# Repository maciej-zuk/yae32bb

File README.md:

# yae32bb
https://hackaday.io/project/25200-yet-another-esp-32-wroom-breakout-board

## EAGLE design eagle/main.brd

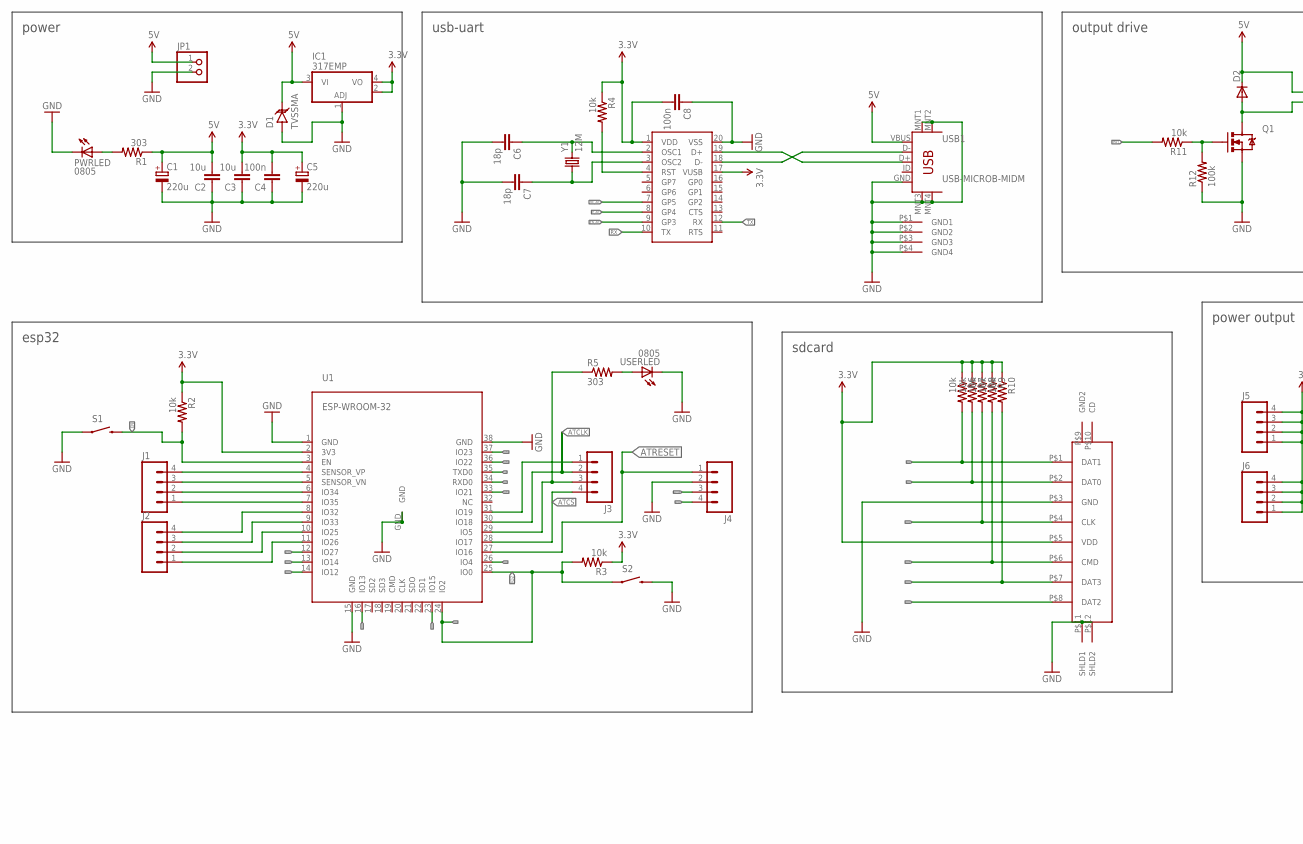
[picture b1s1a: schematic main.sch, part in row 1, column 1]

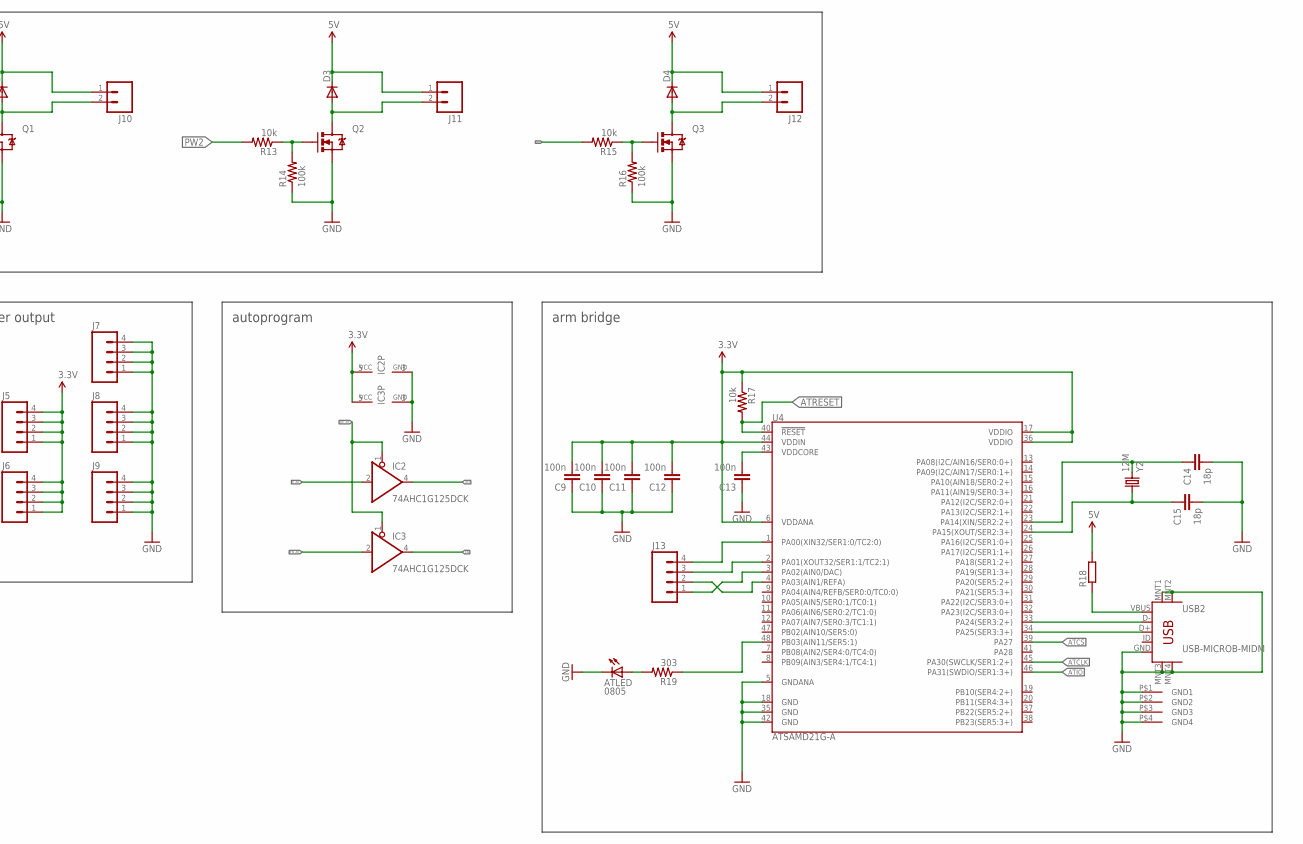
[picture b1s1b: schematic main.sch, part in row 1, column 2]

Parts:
ATLED: 0805; SML0805
C1, C5: 220u; E2-4
C2, C3: 10u; 0805
C4, C8: 100n; 0603-CAP
C6, C7, C14, C15: 18p; 0603-CAP
C9, C10, C11, C12, C13: 100n; C0603K
D1: TVSSMA; SMA-DIODE
D2, D3, D4: DIODE-SOD323-W; SOD323-W
IC1: 317EMP; SOT223
IC2, IC3: 74AHC1G125DCK; SC70-5
J1, J2, J5, J6, J7, J8, J9: M04LONGPADS; 1X04_LONGPADS
J3, J4, J13: M041.27MM; 1X04-1.27MM
J10, J11, J12: M02LOCK_LONGPADS; 1X02_LOCK_LONGPADS
JP1: PINHD-1X2; 1X02
PWRLED: 0805; SML0805
Q1, Q2, Q3: MOSFET-NCHANNELBSS138; SOT23-3
R1, R5, R19: 303; 0805
R2, R3, R4, R6, R7, R8, R9, R10, R11, R13, R15, R17: 10k; 0805
R12, R14, R16: 100k; 0805
R18: R-EU_R2010W; R2010W
S1, S2: SWITCH-MOMENTARY-2SMD; TACTILE-SWITCH-SMD
U1: ESP-WROOM-32
U2: MCP2200; SO20W
U3: MICROSD
U4: ATSAMD21G-A; TQFP-48
USB1, USB2: USB-MICROB-MIDM; USB-B-MICRO-MIDM
USERLED: 0805; SML0805
Y1, Y2: 12M; CRYSTAL-TXC-7A

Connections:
3.3V: C3.2, C4.2, C5.+, C8.2, C9.2, C10.2, C11.2, C12.2, IC1.2 (VO2), IC1.4 (VO), IC2.5 (VCC), IC3.5 (VCC), J5.1, J5.2, J5.3, J5.4, J6.1, J6.2, J6.3, J6.4, R2.1, R3.1, R4.1, R6.1, R7.1, R8.1, R9.1, R10.1, R17.1, U1.2 (3V3), U2.1 (VDD), U2.17 (VUSB), U3.P$5 (VDD), U4.6 (VDDANA), U4.17 (VDDIO), U4.36 (VDDIO), U4.44 (VDDIN)
5V: C1.+, C2.2, D1.C, D2.C, D3.C, D4.C, IC1.3 (VI), J10.1, J11.1, J12.1, JP1.1, R1.1, R18.2, USB1.VBUS
ATCLK: J3.2, J4.3, U1.30 (IO18), U4.45 (PA30(SWCLK/SER1:2+))
ATCS: J3.4, U1.28 (IO17), U4.39 (PA27)
ATIO: J4.4, U1.12 (IO27), U4.46 (PA31(SWDIO/SER1:3+))
ATRESET: J4.1, R17.2, U1.27 (IO16), U4.40 (!RESET!)
D+: U2.19 (D+), USB1.D+
D-: U2.18 (D-), USB1.D-
EN: IC3.4 (O), R2.2, S1.3 (2), U1.3 (EN)
EN_AP: IC3.2 (I), U2.9 (GP3)
GND: ATLED.C, C1.-, C2.1, C3.1, C4.1, C5.-, C6.2, C7.2, C8.1, C9.1, C10.1, C11.1, C12.1, C13.1, C14.2, C15.2, D1.A, IC1.1 (ADJ), IC2.3 (GND), IC3.3 (GND), J4.2, J7.1, J7.2, J7.3, J7.4, J8.1, J8.2, J8.3, J8.4, J9.1, J9.2, J9.3, J9.4, JP1.2, PWRLED.C, Q1.2 (S), Q2.2 (S), Q3.2 (S), R12.1, R14.1, R16.1, S1.1, S2.3 (2), U1.1 (GND), U1.15 (GND), U1.38 (GND), U1.GND, U2.20 (VSS), U3.P$3 (GND), U3.P$11 (SHLD1), U3.P$12 (SHLD2), U4.5 (GNDANA), U4.18 (GND), U4.35 (GND), U4.42 (GND), USB1.GND, USB1.MNT1 (MTN1), USB1.MNT2 (MTN2), USB1.MNT3 (MTN3), USB1.MNT4 (MTN4), USB1.P$1 (GND1), USB1.P$2 (GND2), USB1.P$3 (GND3), USB1.P$4 (GND4), USB2.GND, USB2.MNT1 (MTN1), USB2.MNT2 (MTN2), USB2.MNT3 (MTN3), USB2.MNT4 (MTN4), USB2.P$1 (GND1), USB2.P$2 (GND2), USB2.P$3 (GND3), USB2.P$4 (GND4), USERLED.C
IO2: IC2.4 (O), R3.2, R7.2, S2.1, U1.24 (IO2), U1.25 (IO0), U3.P$2 (DAT0)
IO4: R6.2, U1.26 (IO4), U3.P$1 (DAT1)
IO12: U1.14 (IO12), U3.P$8 (DAT2)
IO13: R10.2, U1.16 (IO13), U3.P$7 (DAT3)
IO14: R8.2, U1.13 (IO14), U3.P$4 (CLK)
IO15: R9.2, U1.23 (IO15), U3.P$6 (CMD)
unnamed: J3.1, U1.31 (IO19)
unnamed: R19.1, U4.48 (PB03(AIN11/SER5:1))
unnamed: R5.2, USERLED.A
unnamed: ATLED.A, R19.2
unnamed: J3.3, R5.1, U1.29 (IO5)
unnamed: J13.4, U4.1 (PA00(XIN32/SER1:0/TC2:0))
unnamed: PWRLED.A, R1.2
unnamed: J13.3, U4.2 (PA01(XOUT32/SER1:1/TC2:1))
unnamed: C13.2, U4.43 (VDDCORE)
unnamed: U4.33 (PA24(SER3:2+)), USB2.D-
unnamed: U4.34 (PA25(SER3:3+)), USB2.D+
unnamed: R18.1, USB2.VBUS
unnamed: J13.1, U4.3 (PA02(AIN0/DAC))
unnamed: J13.2, U4.4 (PA03(AIN1/REFA))
unnamed: D2.A, J10.2, Q1.3 (D)
unnamed: D3.A, J11.2, Q2.3 (D)
unnamed: Q2.1 (G), R13.1, R14.2
unnamed: R4.2, U2.4 (RST)
unnamed: C15.1, U4.24 (PA15(XOUT/SER2:3+)), Y2.P$1 (1)
unnamed: Q1.1 (G), R11.1, R12.2
unnamed: C6.1, U2.2 (OSC1), Y1.P$2 (2)
unnamed: C7.1, U2.3 (OSC2), Y1.P$1 (1)
unnamed: J1.4, U1.4 (SENSOR_VP)
unnamed: J1.3, U1.5 (SENSOR_VN)
unnamed: J1.2, U1.6 (IO34)
unnamed: J1.1, U1.7 (IO35)
unnamed: J2.4, U1.8 (IO32)
unnamed: J2.3, U1.9 (IO33)
unnamed: J2.2, U1.10 (IO25)
unnamed: J2.1, U1.11 (IO26)
unnamed: D4.A, J12.2, Q3.3 (D)
unnamed: Q3.1 (G), R15.1, R16.2
unnamed: C14.1, U4.23 (PA14(XIN/SER2:2+)), Y2.P$2 (2)
OE_AP: IC2.1 (OE), IC3.1 (OE), U2.7 (GP5)
PW1: R11.2, U1.37 (IO23)
PW2: R13.2, U1.36 (IO22)
PW3: R15.2, U1.33 (IO21)
P_AP: IC2.2 (I), U2.8 (GP4)
RX: U1.34 (RXD0), U2.10 (TX)
TX: U1.35 (TXD0), U2.12 (RX)

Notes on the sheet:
power
autoprogram
power output
sdcard
output drive
usb-uart
esp32
arm bridge

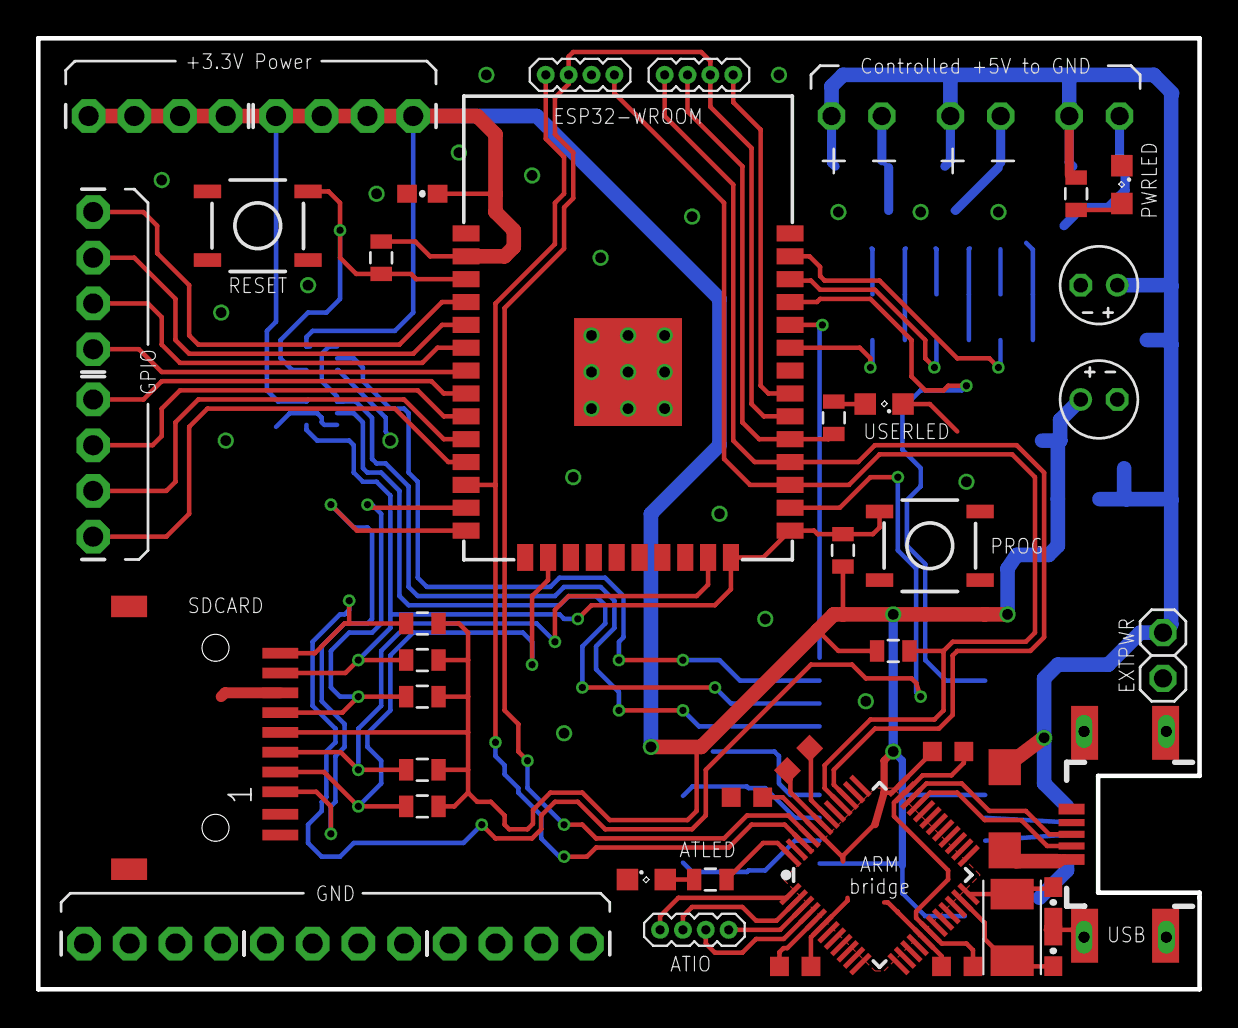
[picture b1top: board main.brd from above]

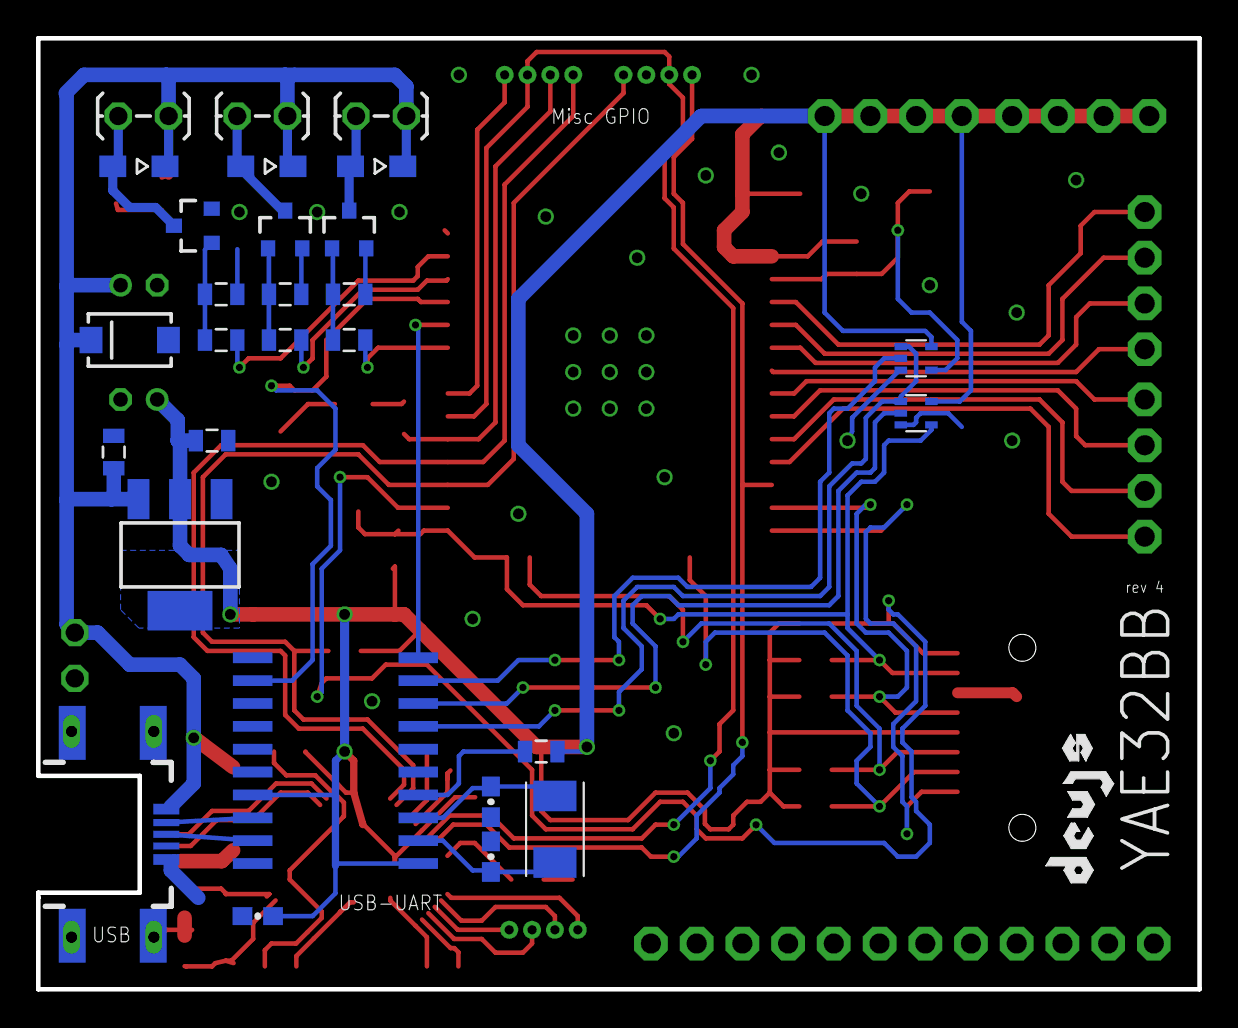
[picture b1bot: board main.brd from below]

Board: 2 copper layers, 64.5 x 52.8 mm, 72 parts (29 on the bottom side), 57 nets.

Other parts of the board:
U$2: DEVJS

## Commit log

2017-06-02 board schematics
2017-07-04 rev4

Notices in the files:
parts and their libraries:
SparkFun-Capacitors: Licensing: Creative Commons ShareAlike 4.0 International - https://creativecommons.org/licenses/by-sa/4.0
